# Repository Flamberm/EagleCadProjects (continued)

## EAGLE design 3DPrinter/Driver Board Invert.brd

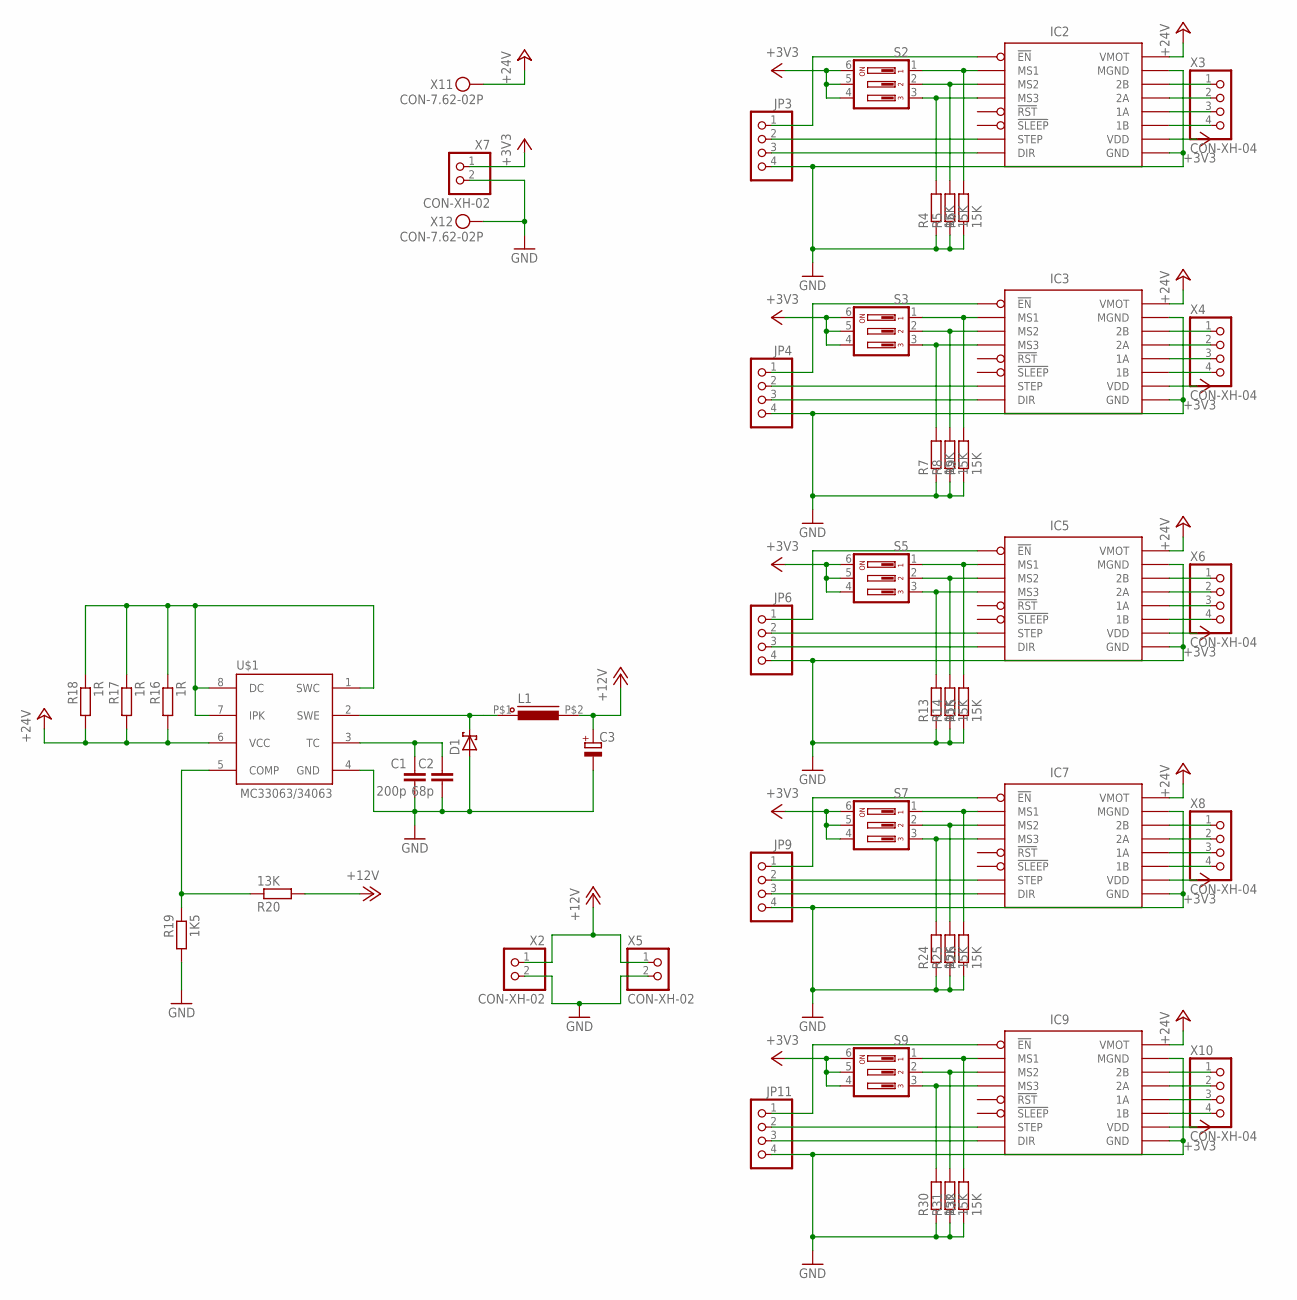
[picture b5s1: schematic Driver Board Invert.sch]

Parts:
C1: 200p; C0805
C2: 68p; C0805
C3: CAP-POL_E3.5-8; E3,5-8
D1: DIODE-SH_SMA; DO214AC
IC2, IC3, IC5, IC7, IC9: STEP-DRVST820-REV; DRV-ST820-REV
JP3, JP4, JP6, JP9, JP11: PINHD-1X4; 1X04
L1: INDUCTORCW68; CW68
R4, R5, R6, R7, R8, R9, R13, R14, R15, R24, R25, R26, R30, R31, R32: 15K; RESC2012X50
R16, R17, R18: 1R; R0805
R19: 1K5; R0805
R20: 13K; R0805
S2, S3, S5, S7, S9: SW-DIP03S; DIP03YL
U$1: MC33063/MC34063P; DIL08
X1: CON-7.62-02P; KF25C-7.62-02P-13
X2, X5, X7: CON-XH-02; XH-02
X3, X4, X6, X8, X10: CON-XH-04; XH-04

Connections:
+3V3: IC2.VDD, IC3.VDD, IC5.VDD, IC7.VDD, IC9.VDD, S2.4, S2.5, S2.6, S3.4, S3.5, S3.6, S5.4, S5.5, S5.6, S7.4, S7.5, S7.6, S9.4, S9.5, S9.6, X7.1
+12V: C3.+, L1.P$2 (2), R20.2, X2.1, X5.1
+24V: IC2.VM (VMOT), IC3.VM (VMOT), IC5.VM (VMOT), IC7.VM (VMOT), IC9.VM (VMOT), R16.2, R17.2, R18.2, U$1.6 (VCC), X1.P$1
GND: C1.2, C2.2, C3.-, D1.A, IC2.GND@1 (MGND), IC2.GND@2 (GND), IC3.GND@1 (MGND), IC3.GND@2 (GND), IC5.GND@1 (MGND), IC5.GND@2 (GND), IC7.GND@1 (MGND), IC7.GND@2 (GND), IC9.GND@1 (MGND), IC9.GND@2 (GND), JP3.4, JP4.4, JP6.4, JP9.4, JP11.4, R4.1, R5.1, R6.1, R7.1, R8.1, R9.1, R13.1, R14.1, R15.1, R19.2, R24.1, R25.1, R26.1, R30.1, R31.1, R32.1, U$1.4 (GND), X1.P$2, X2.2, X5.2, X7.2
unnamed: IC2.EN (!EN), JP3.1
unnamed: IC2.STEP, JP3.2
unnamed: IC2.DIR, JP3.3
unnamed: IC2.1B (2B), X3.1
unnamed: IC2.2B (2A), X3.2
unnamed: IC2.2A (1A), X3.3
unnamed: IC2.1A (1B), X3.4
unnamed: IC2.MS0 (MS1), R6.2, S2.1
unnamed: IC2.MS1 (MS2), R5.2, S2.2
unnamed: IC2.MS2 (MS3), R4.2, S2.3
unnamed: IC3.EN (!EN), JP4.1
unnamed: IC3.STEP, JP4.2
unnamed: IC3.DIR, JP4.3
unnamed: IC3.1B (2B), X4.1
unnamed: IC3.2B (2A), X4.2
unnamed: IC3.2A (1A), X4.3
unnamed: IC3.1A (1B), X4.4
unnamed: IC3.MS0 (MS1), R9.2, S3.1
unnamed: IC3.MS1 (MS2), R8.2, S3.2
unnamed: IC3.MS2 (MS3), R7.2, S3.3
unnamed: IC5.EN (!EN), JP6.1
unnamed: IC5.STEP, JP6.2
unnamed: IC5.DIR, JP6.3
unnamed: IC5.1B (2B), X6.1
unnamed: IC5.2B (2A), X6.2
unnamed: IC5.2A (1A), X6.3
unnamed: IC5.1A (1B), X6.4
unnamed: IC5.MS0 (MS1), R15.2, S5.1
unnamed: IC5.MS1 (MS2), R14.2, S5.2
unnamed: IC5.MS2 (MS3), R13.2, S5.3
unnamed: C1.1, C2.1, U$1.3 (TC)
unnamed: R16.1, R17.1, R18.1, U$1.1 (SWC), U$1.7 (IPK), U$1.8 (DC)
unnamed: D1.C, L1.P$1 (1), U$1.2 (SWE)
unnamed: R19.1, R20.1, U$1.5 (COMP)
unnamed: IC7.EN (!EN), JP9.1
unnamed: IC7.STEP, JP9.2
unnamed: IC7.DIR, JP9.3
unnamed: IC7.1B (2B), X8.1
unnamed: IC7.2B (2A), X8.2
unnamed: IC7.2A (1A), X8.3
unnamed: IC7.1A (1B), X8.4
unnamed: IC7.MS0 (MS1), R26.2, S7.1
unnamed: IC7.MS1 (MS2), R25.2, S7.2
unnamed: IC7.MS2 (MS3), R24.2, S7.3
unnamed: IC9.EN (!EN), JP11.1
unnamed: IC9.STEP, JP11.2
unnamed: IC9.DIR, JP11.3
unnamed: IC9.1B (2B), X10.1
unnamed: IC9.2B (2A), X10.2
unnamed: IC9.2A (1A), X10.3
unnamed: IC9.1A (1B), X10.4
unnamed: IC9.MS0 (MS1), R32.2, S9.1
unnamed: IC9.MS1 (MS2), R31.2, S9.2
unnamed: IC9.MS2 (MS3), R30.2, S9.3

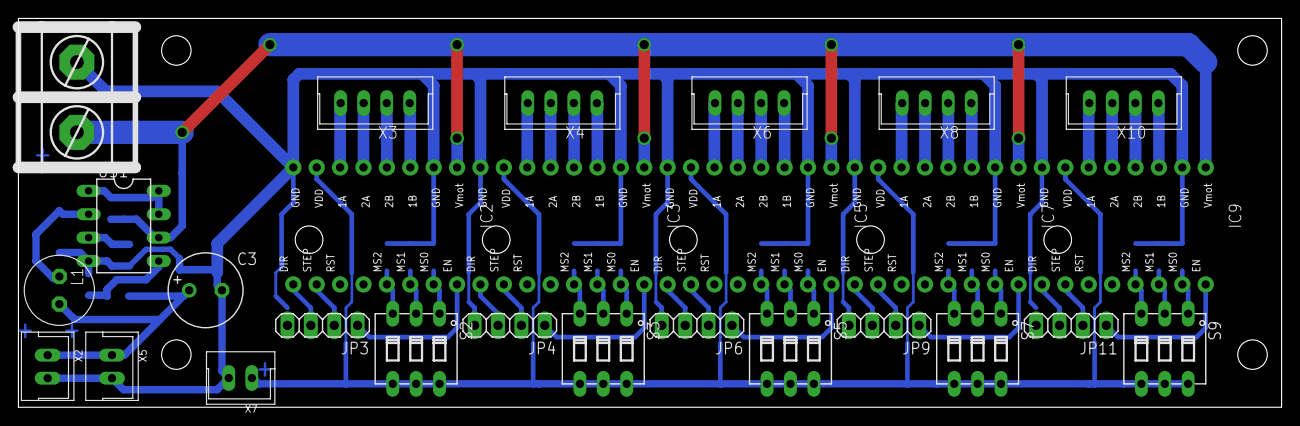
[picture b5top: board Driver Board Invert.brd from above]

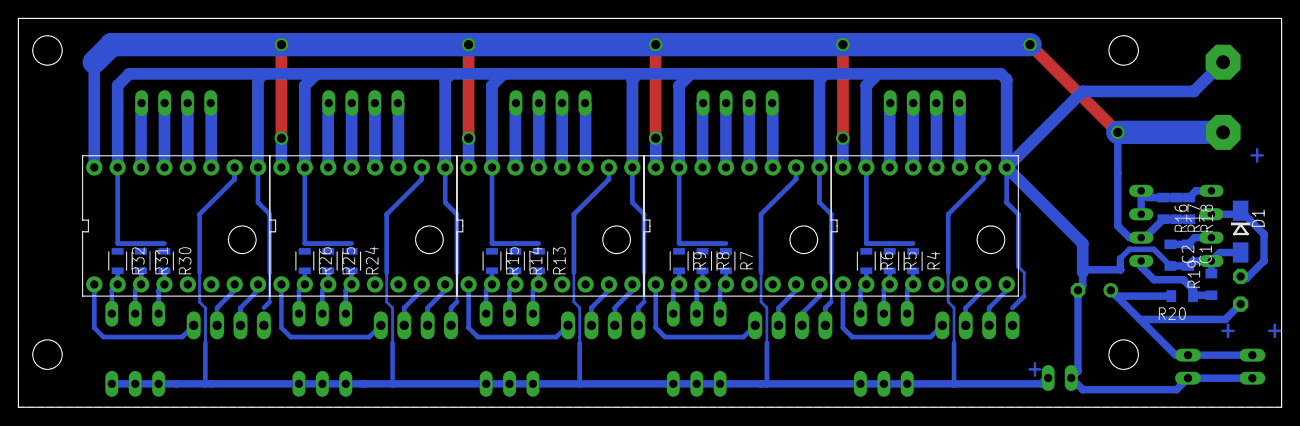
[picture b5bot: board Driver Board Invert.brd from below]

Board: 2 copper layers, 137.1 x 42.2 mm, 50 parts (23 on the bottom side), 58 nets.

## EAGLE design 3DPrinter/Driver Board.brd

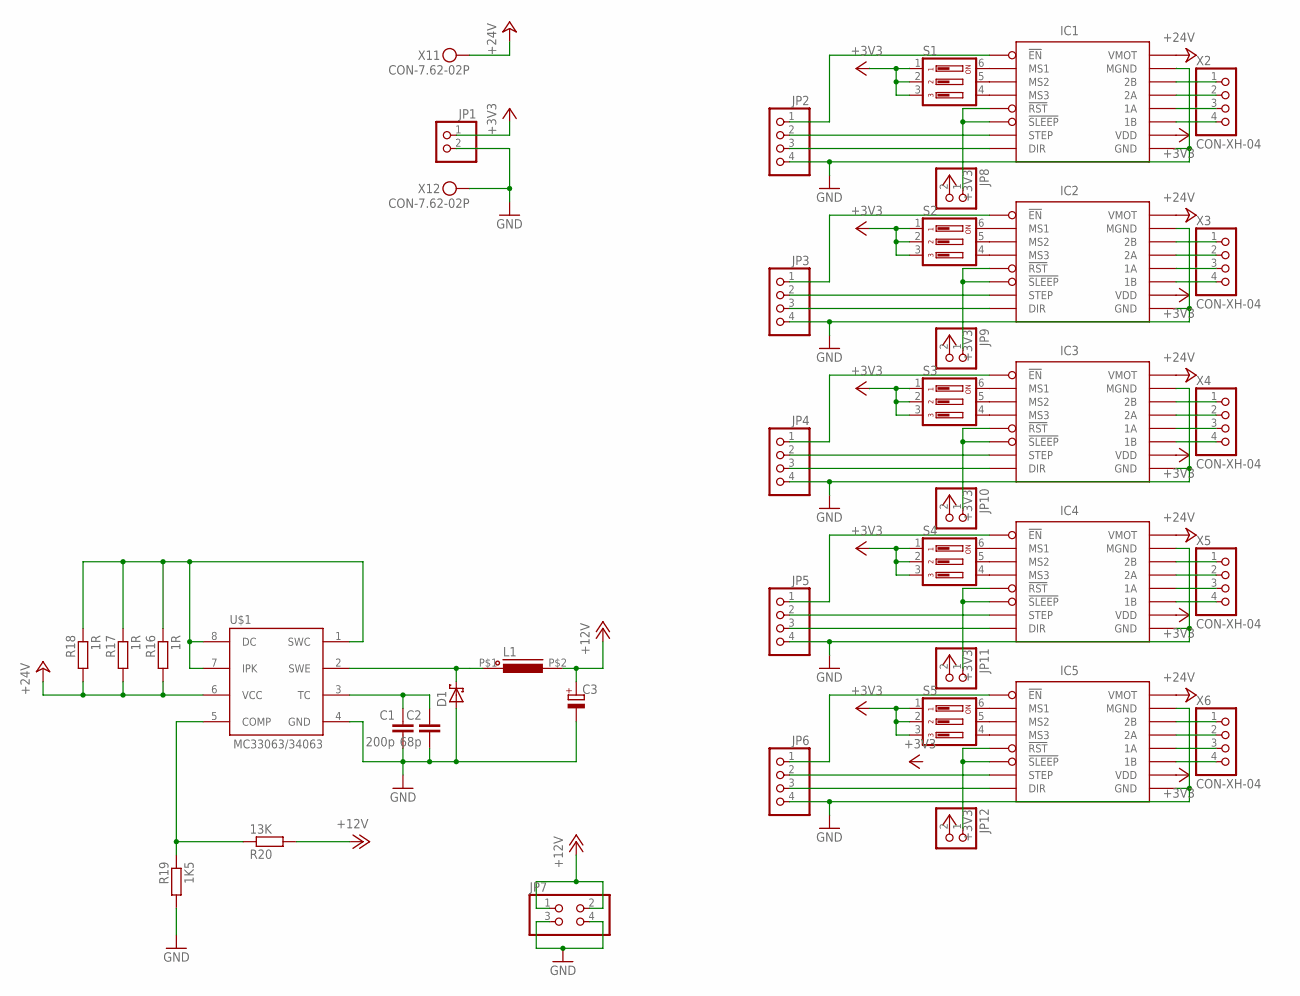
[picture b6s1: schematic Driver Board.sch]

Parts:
C1: 200p; C0805
C2: 68p; C0805
C3: CAP-POL_E3.5-8; E3,5-8
D1: DIODE-SH_SMA; DO214AC
IC1, IC2, IC3, IC4, IC5: STEP-DRV; DRV-BRK
JP1, JP8, JP9, JP10, JP11, JP12: PINHD-1X2; 1X02
JP2, JP3, JP4, JP5, JP6: PINHD-1X4; 1X04
JP7: PINHD-2X2; 2X02
L1: INDUCTORCW68; CW68
R16, R17, R18: 1R; R0805
R19: 1K5; R0805
R20: 13K; R0805
S1, S2, S3, S4, S5: SW-DIP03S; DIP03YL
U$1: MC33063/MC34063P; DIL08
X1: CON-7.62-02P; KF25C-7.62-02P-13
X2, X3, X4, X5, X6: CON-XH-04; XH-04

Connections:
+3V3: IC1.P$10 (VDD), IC2.P$10 (VDD), IC3.P$10 (VDD), IC4.P$10 (VDD), IC5.P$10 (VDD), JP1.1, JP8.2, JP9.2, JP10.2, JP11.2, JP12.2, S1.1, S1.2, S1.3, S2.1, S2.2, S2.3, S3.1, S3.2, S3.3, S4.1, S4.2, S4.3, S5.1, S5.2, S5.3
+12V: C3.+, JP7.1, JP7.2, L1.P$2 (2), R20.2
+24V: IC1.P$16 (VMOT), IC2.P$16 (VMOT), IC3.P$16 (VMOT), IC4.P$16 (VMOT), IC5.P$16 (VMOT), R16.2, R17.2, R18.2, U$1.6 (VCC), X1.P$1
GND: C1.2, C2.2, C3.-, D1.A, IC1.P$9 (GND), IC1.P$15 (MGND), IC2.P$9 (GND), IC2.P$15 (MGND), IC3.P$9 (GND), IC3.P$15 (MGND), IC4.P$9 (GND), IC4.P$15 (MGND), IC5.P$9 (GND), IC5.P$15 (MGND), JP1.2, JP2.4, JP3.4, JP4.4, JP5.4, JP6.4, JP7.3, JP7.4, R19.2, U$1.4 (GND), X1.P$2
unnamed: IC1.P$1 (!EN), JP2.1
unnamed: IC1.P$7 (STEP), JP2.2
unnamed: IC1.P$8 (DIR), JP2.3
unnamed: IC1.P$14 (2B), X2.1
unnamed: IC2.P$8 (DIR), JP3.3
unnamed: IC2.P$7 (STEP), JP3.2
unnamed: IC2.P$1 (!EN), JP3.1
unnamed: IC1.P$13 (2A), X2.2
unnamed: IC3.P$8 (DIR), JP4.3
unnamed: IC3.P$7 (STEP), JP4.2
unnamed: IC3.P$1 (!EN), JP4.1
unnamed: IC1.P$12 (1A), X2.3
unnamed: IC1.P$11 (1B), X2.4
unnamed: IC4.P$8 (DIR), JP5.3
unnamed: IC4.P$7 (STEP), JP5.2
unnamed: IC4.P$1 (!EN), JP5.1
unnamed: IC2.P$14 (2B), X3.1
unnamed: IC5.P$8 (DIR), JP6.3
unnamed: IC5.P$7 (STEP), JP6.2
unnamed: IC5.P$1 (!EN), JP6.1
unnamed: IC2.P$13 (2A), X3.2
unnamed: IC2.P$12 (1A), X3.3
unnamed: IC2.P$11 (1B), X3.4
unnamed: IC3.P$14 (2B), X4.1
unnamed: IC3.P$13 (2A), X4.2
unnamed: IC3.P$12 (1A), X4.3
unnamed: IC3.P$11 (1B), X4.4
unnamed: IC4.P$14 (2B), X5.1
unnamed: IC4.P$13 (2A), X5.2
unnamed: IC4.P$12 (1A), X5.3
unnamed: IC4.P$11 (1B), X5.4
unnamed: IC5.P$14 (2B), X6.1
unnamed: IC5.P$13 (2A), X6.2
unnamed: IC5.P$12 (1A), X6.3
unnamed: IC5.P$11 (1B), X6.4
unnamed: IC1.P$4 (MS3), S1.4
unnamed: IC1.P$3 (MS2), S1.5
unnamed: IC1.P$2 (MS1), S1.6
unnamed: IC5.P$5 (!RST), IC5.P$6 (!SLEEP), JP12.1
unnamed: IC4.P$5 (!RST), IC4.P$6 (!SLEEP), JP11.1
unnamed: IC3.P$5 (!RST), IC3.P$6 (!SLEEP), JP10.1
unnamed: IC2.P$5 (!RST), IC2.P$6 (!SLEEP), JP9.1
unnamed: IC1.P$5 (!RST), IC1.P$6 (!SLEEP), JP8.1
unnamed: IC2.P$4 (MS3), S2.4
unnamed: IC2.P$3 (MS2), S2.5
unnamed: IC2.P$2 (MS1), S2.6
unnamed: IC3.P$4 (MS3), S3.4
unnamed: IC3.P$3 (MS2), S3.5
unnamed: IC3.P$2 (MS1), S3.6
unnamed: IC4.P$4 (MS3), S4.4
unnamed: C1.1, C2.1, U$1.3 (TC)
unnamed: R16.1, R17.1, R18.1, U$1.1 (SWC), U$1.7 (IPK), U$1.8 (DC)
unnamed: IC4.P$3 (MS2), S4.5
unnamed: D1.C, L1.P$1 (1), U$1.2 (SWE)
unnamed: R19.1, R20.1, U$1.5 (COMP)
unnamed: IC4.P$2 (MS1), S4.6
unnamed: IC5.P$4 (MS3), S5.4
unnamed: IC5.P$3 (MS2), S5.5
unnamed: IC5.P$2 (MS1), S5.6

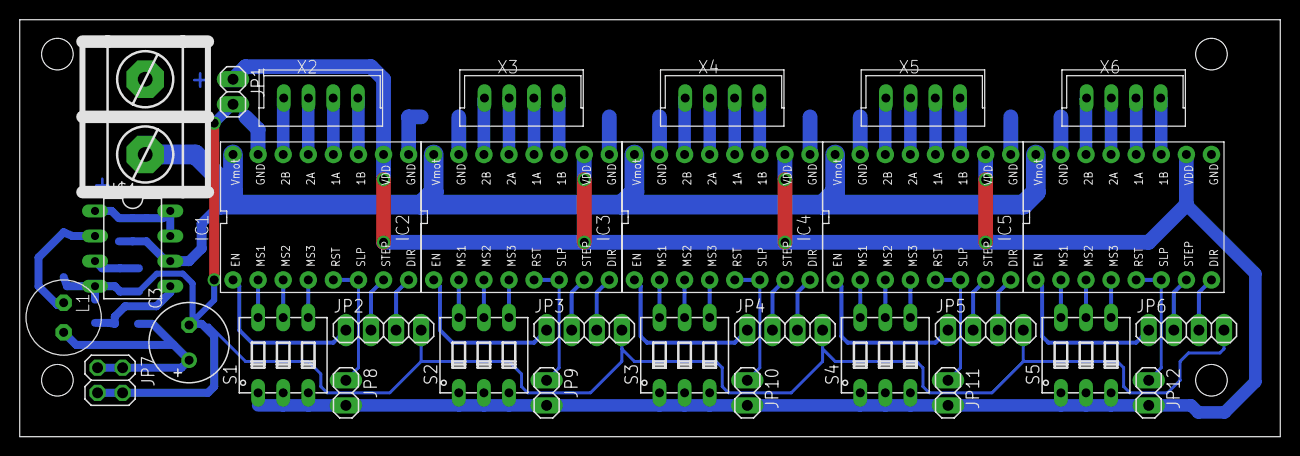
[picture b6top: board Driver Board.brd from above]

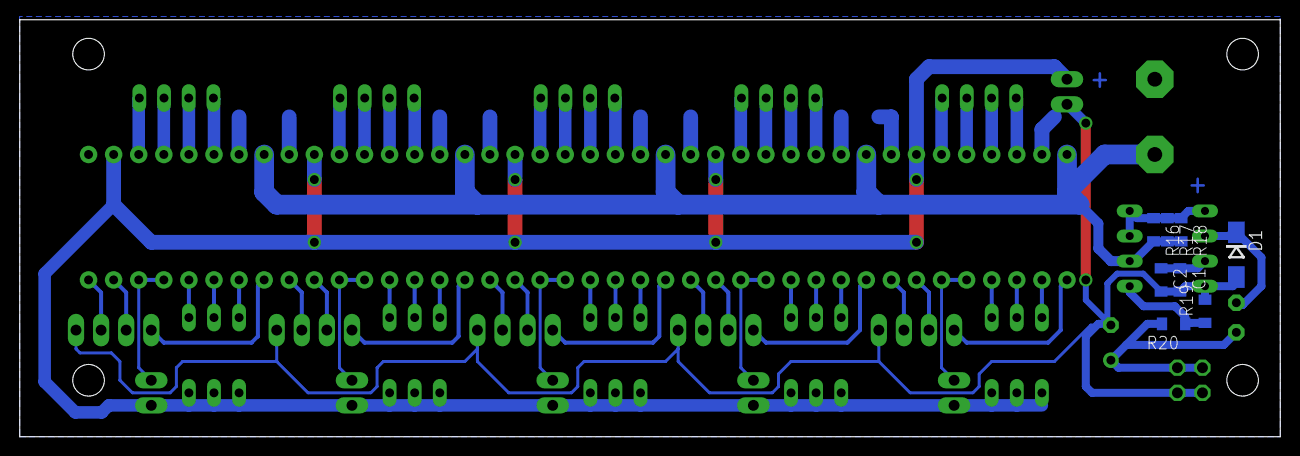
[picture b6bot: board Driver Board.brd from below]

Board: 2 copper layers, 127.6 x 42.2 mm, 39 parts (8 on the bottom side), 63 nets.

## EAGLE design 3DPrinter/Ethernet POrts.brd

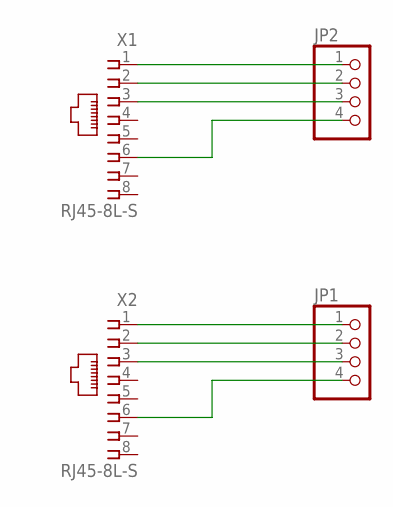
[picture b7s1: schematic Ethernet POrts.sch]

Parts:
JP1, JP2: PINHD-1X4; 1X04
X1, X2: RJ45-8L-S; RJ45-NO-SHIELD

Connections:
unnamed: JP2.1, X1.1
unnamed: JP2.2, X1.2
unnamed: JP2.3, X1.3
unnamed: JP2.4, X1.6
unnamed: JP1.1, X2.1
unnamed: JP1.2, X2.2
unnamed: JP1.3, X2.3
unnamed: JP1.4, X2.6

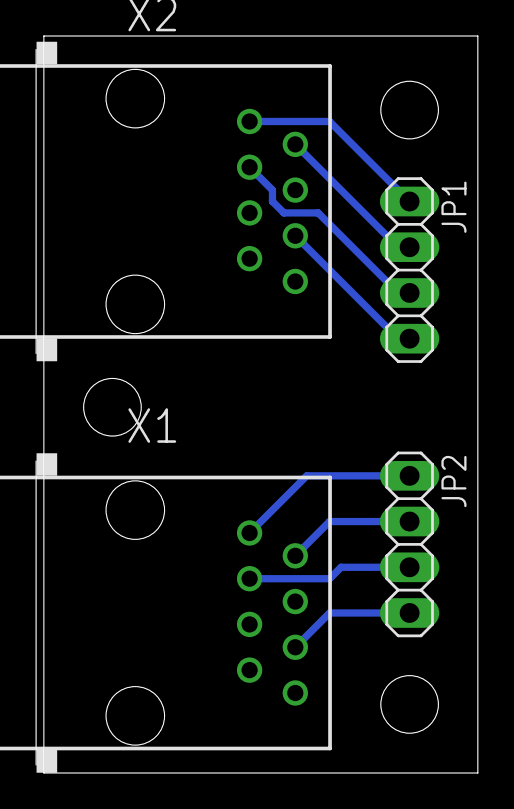
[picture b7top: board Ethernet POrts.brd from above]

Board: 2 copper layers, 24.1 x 40.9 mm, 4 parts (0 on the bottom side), 8 nets.
